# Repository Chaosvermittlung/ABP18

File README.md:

# ABP18
Die Ausbruchplatine 18 ist eine Platine mit der ein Netzwerkkabel auf verschiedene andere Anschlüsse gesteckt werden kann.

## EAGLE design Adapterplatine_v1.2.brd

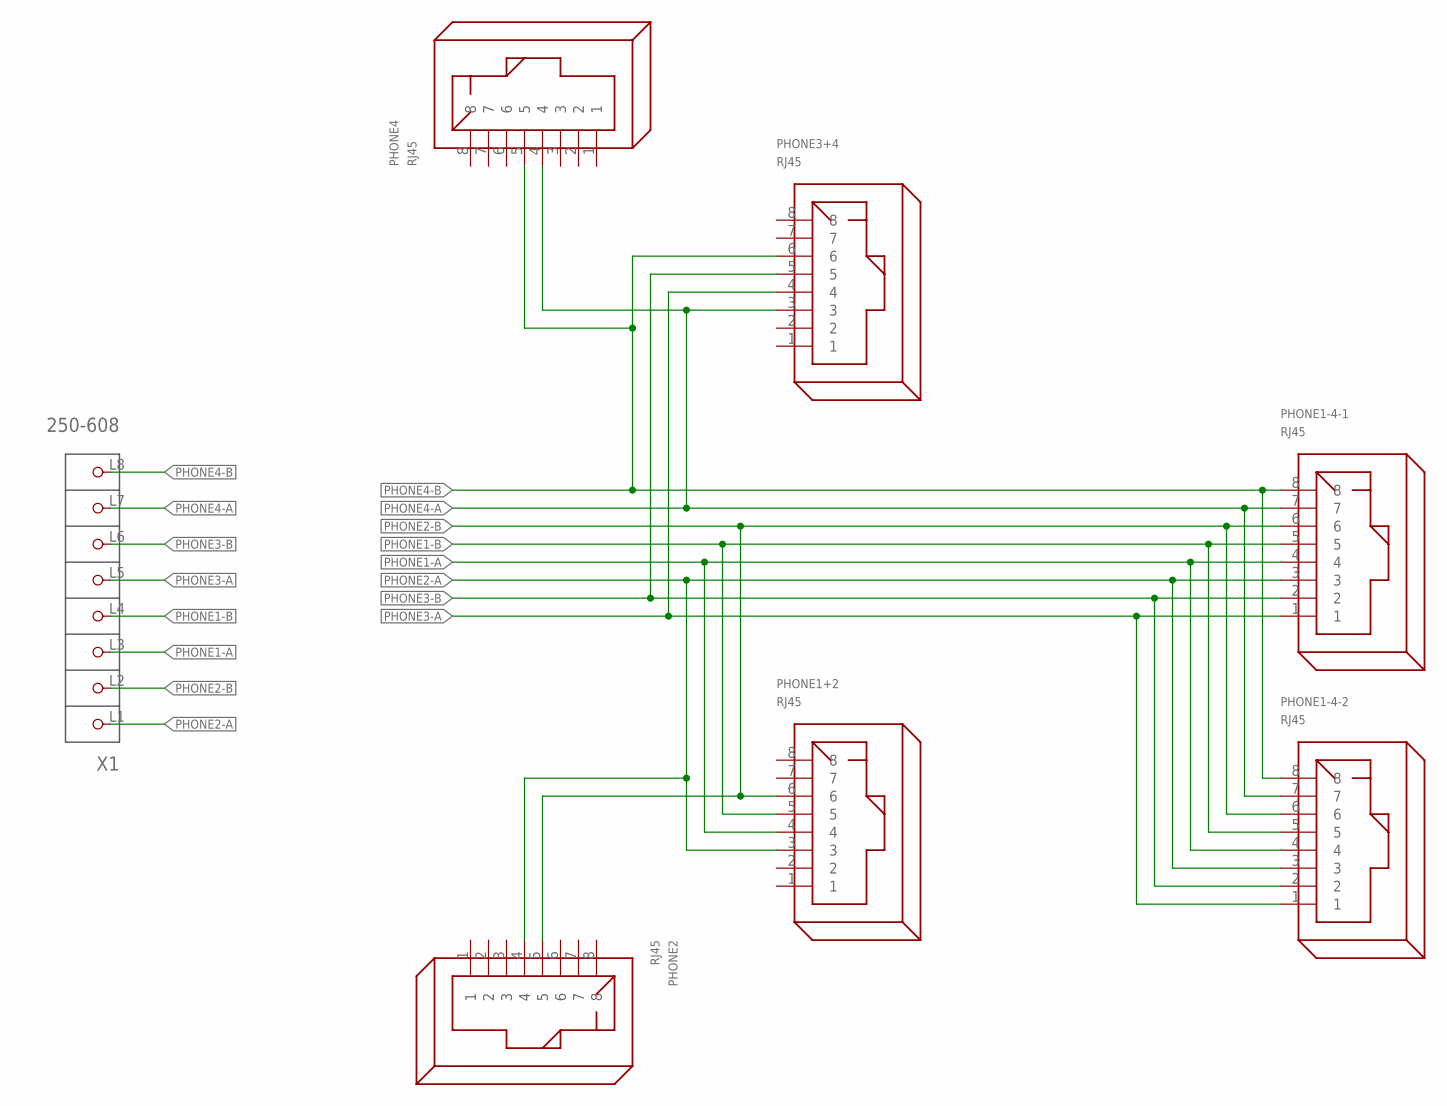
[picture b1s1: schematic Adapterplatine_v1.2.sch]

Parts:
PHONE1+2, PHONE1-4-1, PHONE1-4-2, PHONE2, PHONE3+4, PHONE4: RJ45
X1: 250-608; P-250-608

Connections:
PHONE1-A: PHONE1+2.4, PHONE1-4-1.4, PHONE1-4-2.4, X1.L3 (P3)
PHONE1-B: PHONE1+2.5, PHONE1-4-1.5, PHONE1-4-2.5, X1.L4 (P4)
PHONE2-A: PHONE1+2.3, PHONE1-4-1.3, PHONE1-4-2.3, PHONE2.4, X1.L1 (P1)
PHONE2-B: PHONE1+2.6, PHONE1-4-1.6, PHONE1-4-2.6, PHONE2.5, X1.L2 (P2)
PHONE3-A: PHONE1-4-1.1, PHONE1-4-2.1, PHONE3+4.4, X1.L5 (P5)
PHONE3-B: PHONE1-4-1.2, PHONE1-4-2.2, PHONE3+4.5, X1.L6 (P6)
PHONE4-A: PHONE1-4-1.7, PHONE1-4-2.7, PHONE3+4.3, PHONE4.4, X1.L7 (P7)
PHONE4-B: PHONE1-4-1.8, PHONE1-4-2.8, PHONE3+4.6, PHONE4.5, X1.L8 (P8)

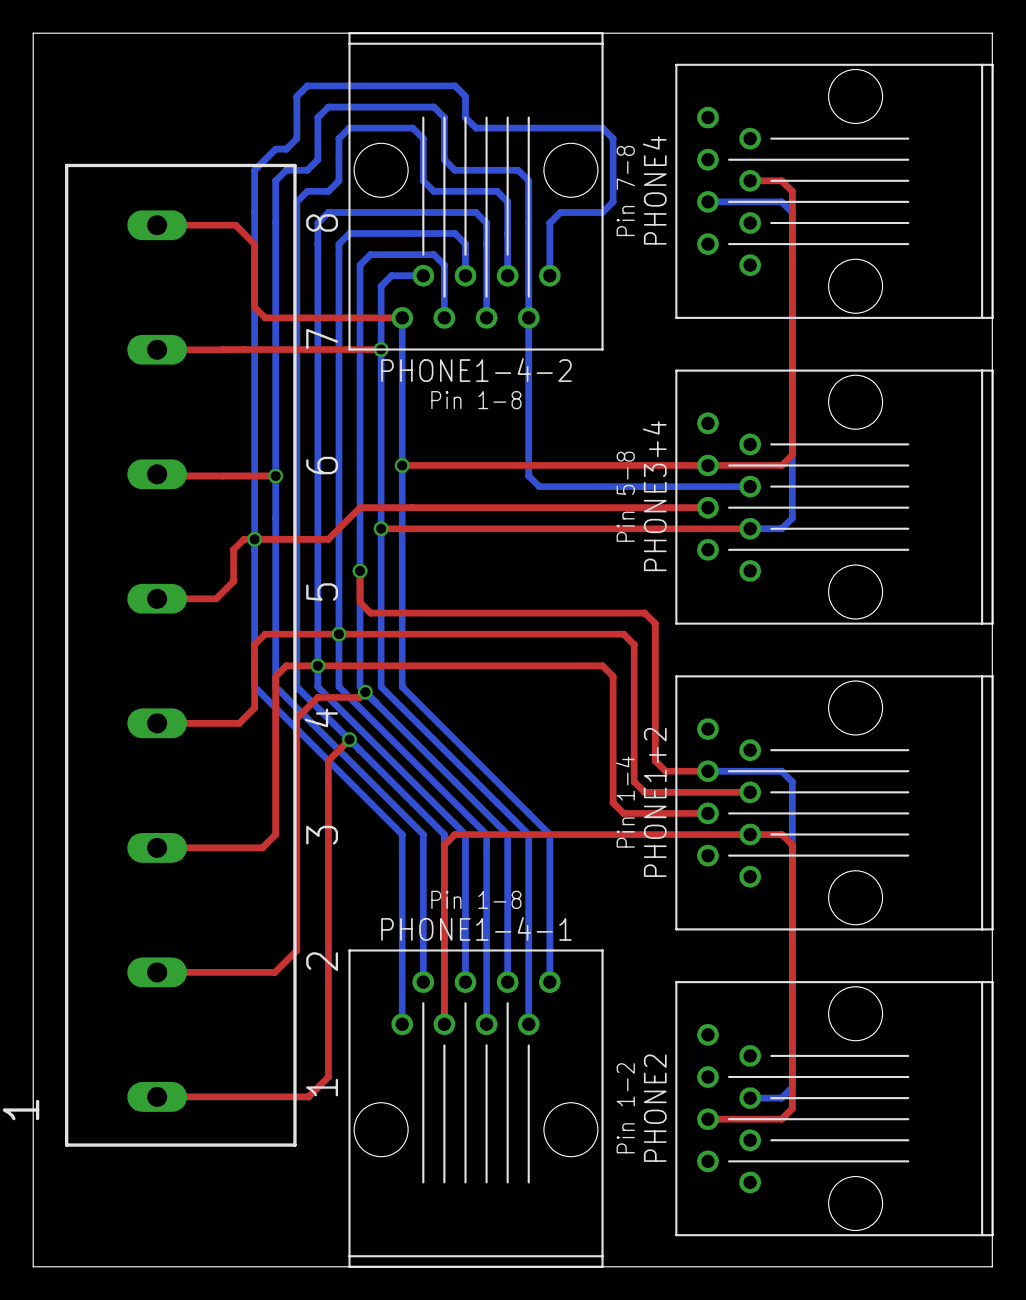
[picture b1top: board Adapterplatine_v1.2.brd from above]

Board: 2 copper layers, 57.8 x 74.3 mm, 7 parts (0 on the bottom side), 8 nets.

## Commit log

2020-10-18 Schematik
